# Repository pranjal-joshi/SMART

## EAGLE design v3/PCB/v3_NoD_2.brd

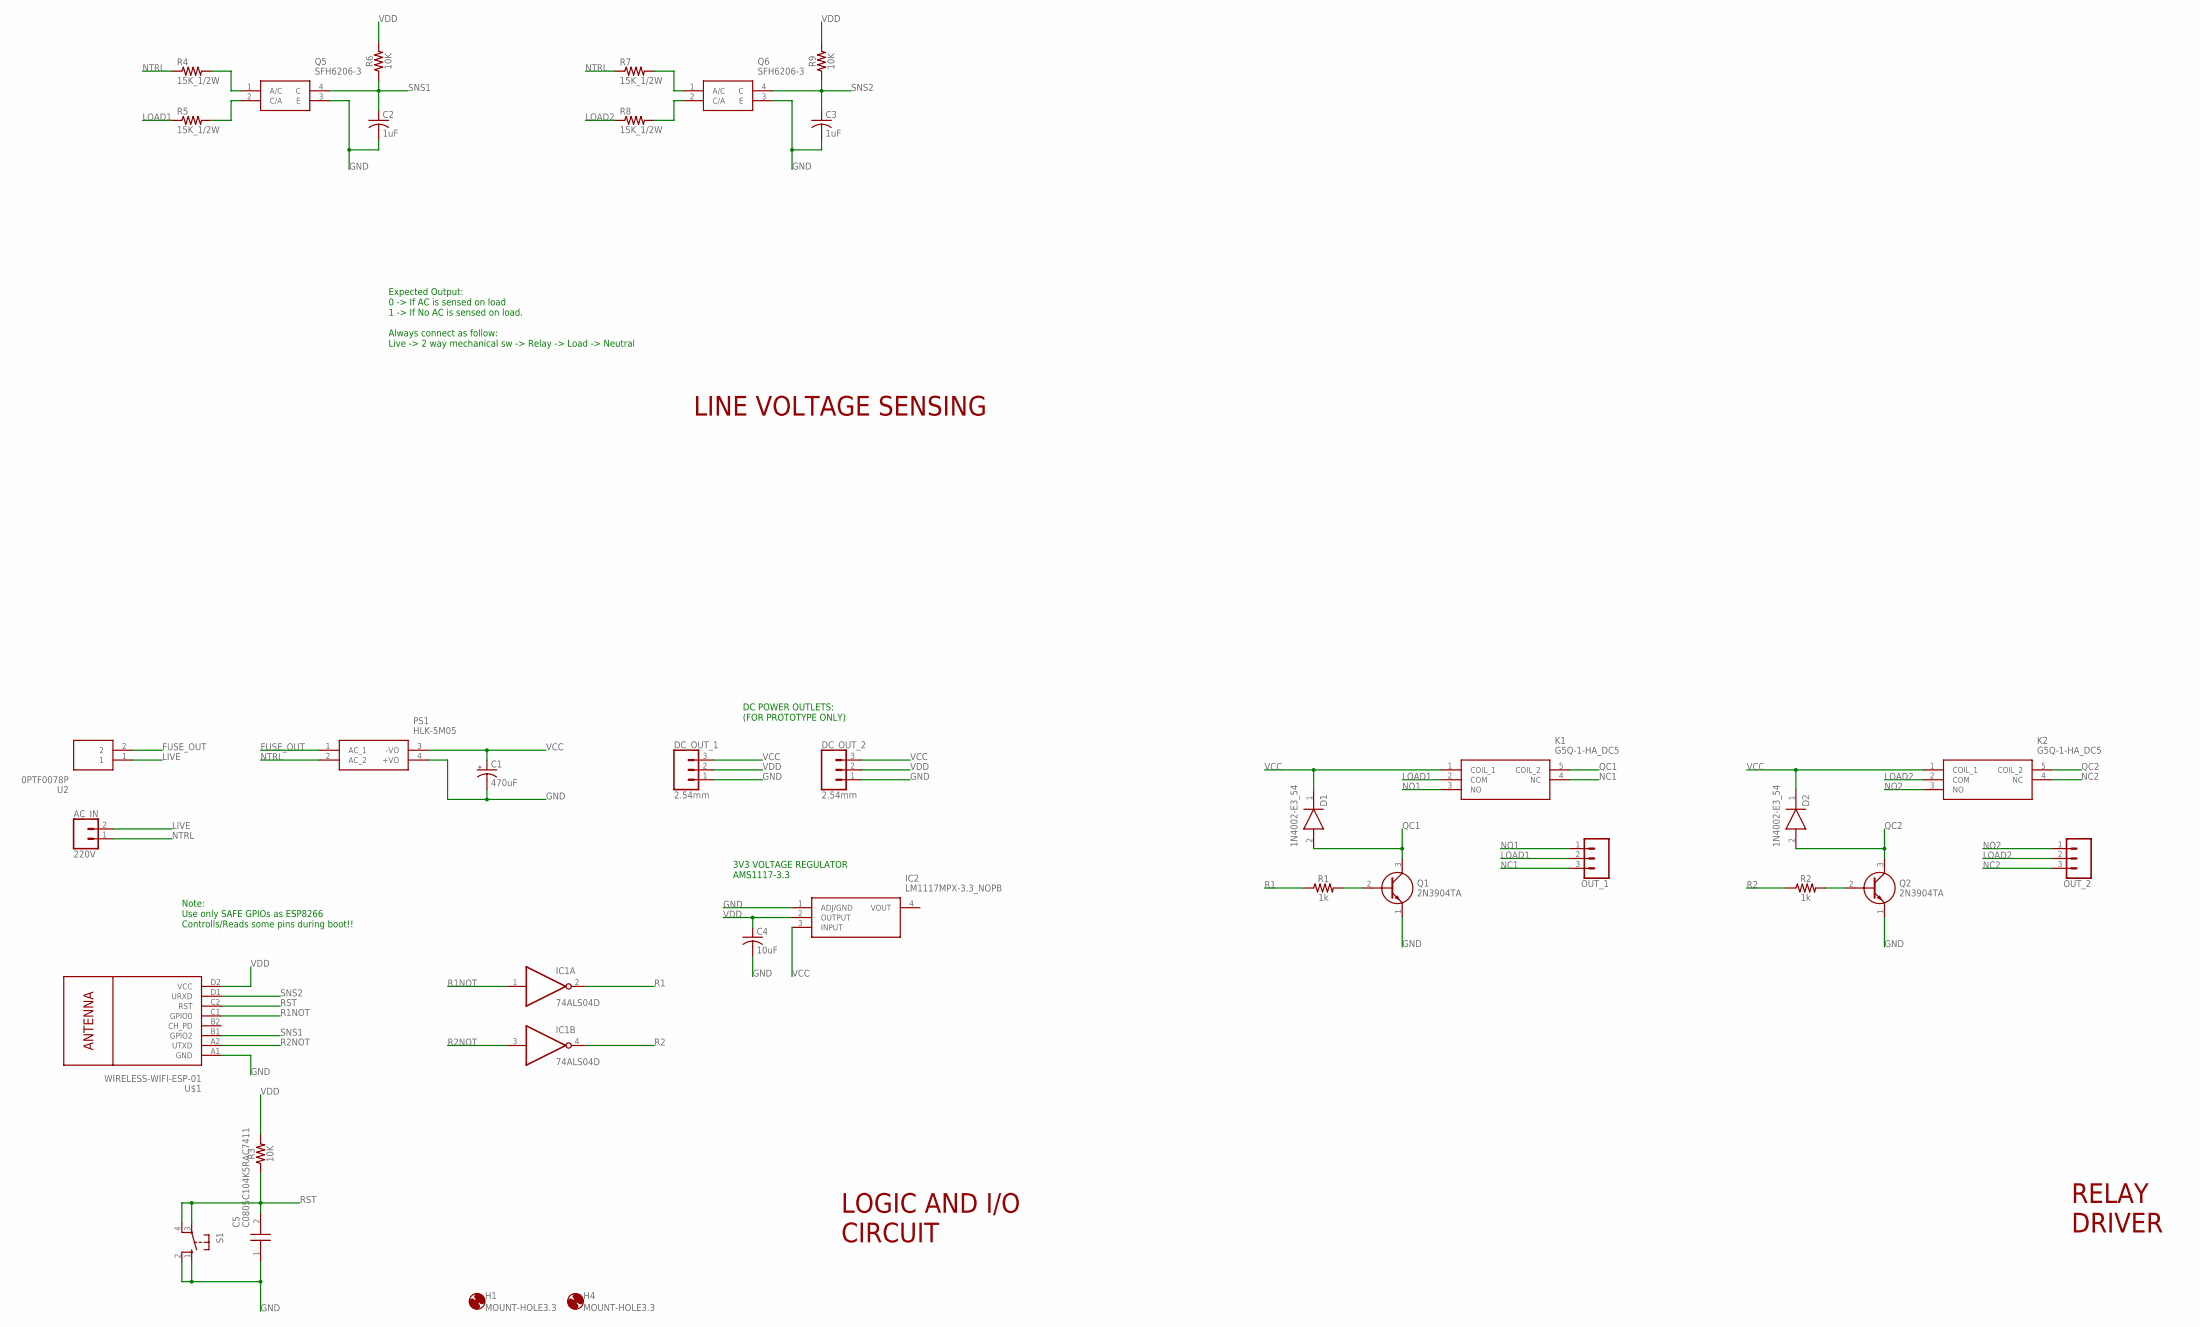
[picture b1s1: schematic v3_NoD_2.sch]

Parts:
AC_IN: 220V; SCREWTERMINAL-5MM-2
C1: 470uF; CPOL-RADIAL-5MM-10MM-KIT
C2, C3: 1uF; C0805
C4: 10uF; C0805
C5: C0805C104K5RAC7411; CAPC2012X88N
D1, D2: 1N4002-E3_54; DIOAD1405W86L465D235
DC_OUT_1, DC_OUT_2: 2.54mm; 1X03
H1, H4: MOUNT-HOLE3.3; 3,3
IC1: 74ALS04D; SO14
IC2: LM1117MPX-3.3_NOPB; SOT230P700X180-4N
K1, K2: G5Q-1-HA_DC5; G5Q1EU12DC
OUT_1, OUT_2: CONN_03-SCREW-5MM; SCREWTERMINAL-5MM-3
PS1: HLK-5M05; HLK5M05
Q1, Q2: 2N3904TA; BC33740TA
Q5, Q6: SFH6206-3; SOP254P1005X410-4N
R1, R2: 1k; 0603
R3, R6, R9: 10K; 0603
R4, R5, R7, R8: 15K_1/2W; R1210
S1: 10-XX; B3F-10XX
U2: 0PTF0078P
U$1: WIRELESS-WIFI-ESP-01

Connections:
FUSE_OUT: PS1.1 (AC_1), U2.2
GND: C1.-, C2.2, C3.2, C4.2, C5.1, DC_OUT_1.1, DC_OUT_2.1, IC1.7 (GND), IC2.1 (ADJ/GND), PS1.4 (+VO), Q1.1 (E), Q2.1 (E), Q5.3 (E), Q6.3 (E), S1.1 (S), S1.2 (S1), U$1.A1 (GND)
LIVE: AC_IN.2, U2.1
LOAD1: K1.2 (COM), OUT_1.2, R5.1
LOAD2: K2.2 (COM), OUT_2.2, R8.1
unnamed: Q5.1 (A/C), R4.2
unnamed: Q5.2 (C/A), R5.2
unnamed: Q6.1 (A/C), R7.2
unnamed: Q1.2 (B), R1.2
unnamed: Q2.2 (B), R2.2
unnamed: Q6.2 (C/A), R8.2
NC1: K1.4 (NC), OUT_1.3
NC2: K2.4 (NC), OUT_2.3
NO1: K1.3 (NO), OUT_1.1
NO2: K2.3 (NO), OUT_2.1
NTRL: AC_IN.1, PS1.2 (AC_2), R4.1, R7.1
QC1: D1.2 (A), K1.5 (COIL_2), Q1.3 (C)
QC2: D2.2 (A), K2.5 (COIL_2), Q2.3 (C)
R1: IC1.2 (O), R1.1
R1NOT: IC1.1 (I), U$1.C1 (GPIO0)
R2: IC1.4 (O), R2.1
R2NOT: IC1.3 (I), U$1.A2 (UTXD)
RST: C5.2, R3.1, S1.3, S1.4 (P1), U$1.C2 (RST)
SNS1: C2.1, Q5.4 (C), R6.1, U$1.B1 (GPIO2)
SNS2: C3.1, Q6.4 (C), R9.1, U$1.D1 (URXD)
VCC: C1.+, D1.1 (K), D2.1 (K), DC_OUT_1.3, DC_OUT_2.3, IC1.14 (VCC), IC2.3 (INPUT), K1.1 (COIL_1), K2.1 (COIL_1), PS1.3 (-VO)
VDD: C4.1, DC_OUT_1.2, DC_OUT_2.2, IC2.2 (OUTPUT), R3.2, R6.2, R9.2, U$1.D2 (VCC)

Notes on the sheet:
LOGIC AND I/O CIRCUIT
LINE VOLTAGE SENSING
RELAY DRIVER
DC POWER OUTLETS: (FOR PROTOTYPE ONLY)
Expected Output: 0 -> If AC is sensed on load 1 -> If No AC is sensed on load. Always connect as follow: Live -> 2 way mechanical sw -> Relay -> Load -> Neutral
Note: Use only SAFE GPIOs as ESP8266 Controlls/Reads some pins during boot!!
3V3 VOLTAGE REGULATOR AMS1117-3.3

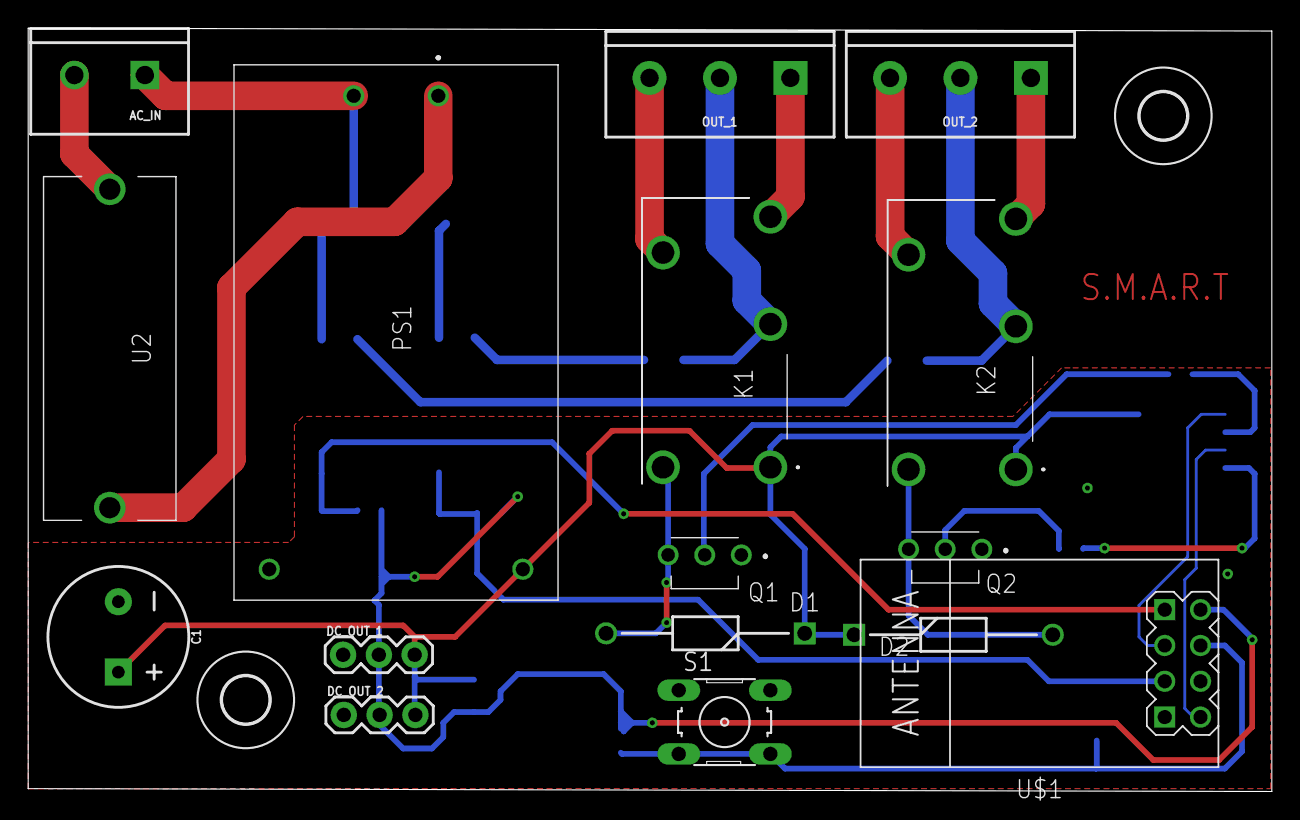
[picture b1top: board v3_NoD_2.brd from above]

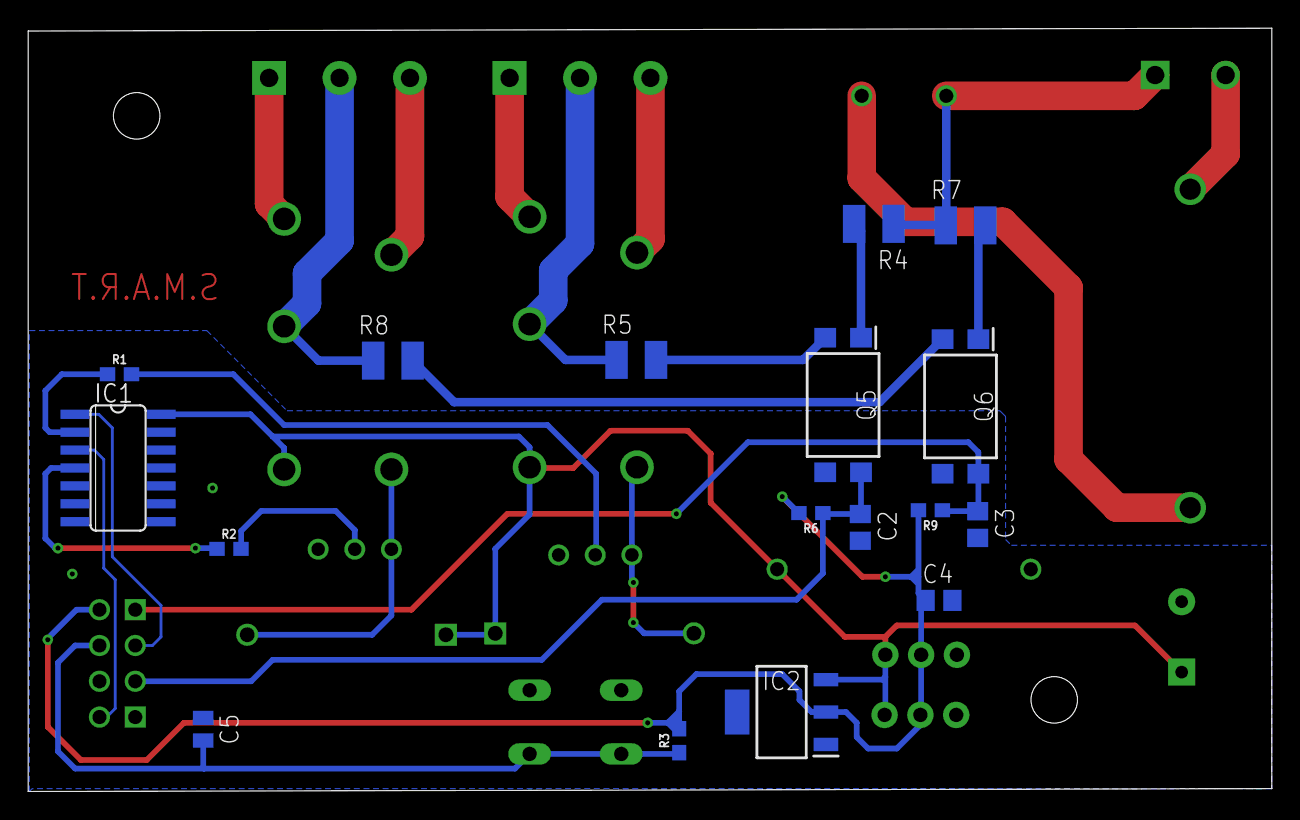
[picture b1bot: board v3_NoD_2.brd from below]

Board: 2 copper layers, 88.3 x 54.2 mm, 35 parts (17 on the bottom side), 27 nets.

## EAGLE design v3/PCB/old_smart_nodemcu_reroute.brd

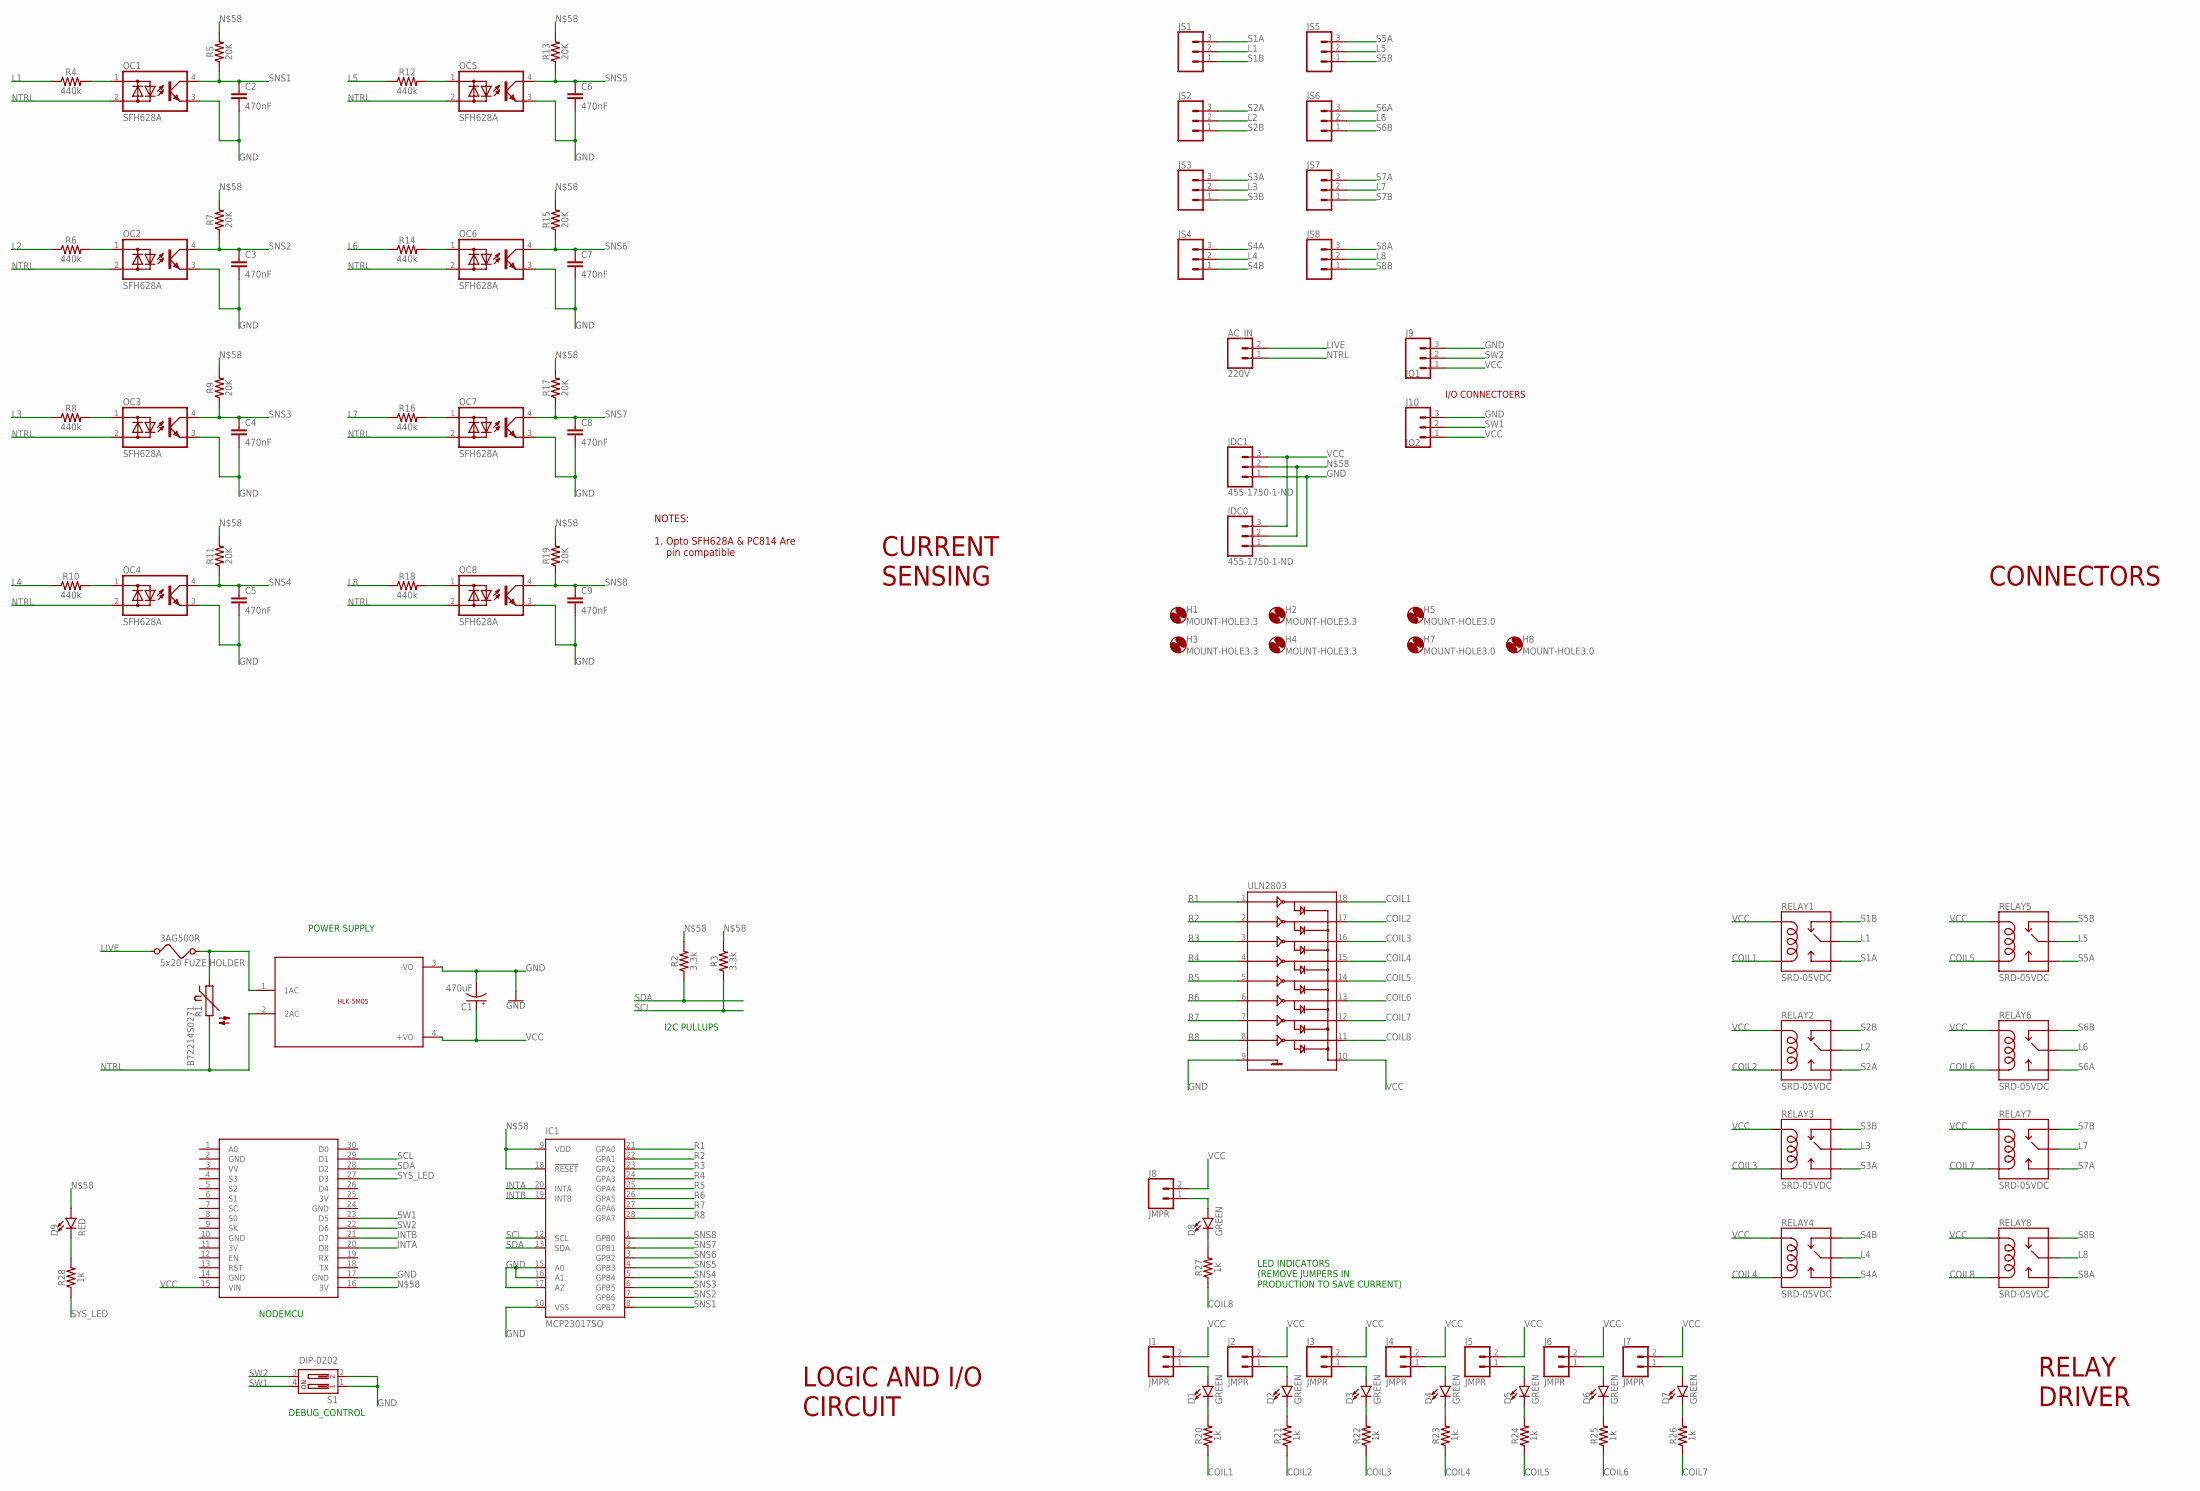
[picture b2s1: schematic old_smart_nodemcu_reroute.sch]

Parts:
3AG500R: 5x20 FUZE HOLDER; FUSE
AC_IN: 220V; SCREWTERMINAL-5MM-2
C1: 470uF; E3,5-8
C2, C3, C4, C5, C6, C7, C8, C9: 470nF; 0603
D1, D2, D3, D4, D5, D6, D7, D8: GREEN; LED-0603
D9: RED; LED-0603
H1, H2, H3, H4: MOUNT-HOLE3.3; 3,3
H5, H7, H8: MOUNT-HOLE3.0; 3,0
IC1: MCP23017SO; SO28W
J1, J2, J3, J4, J5, J6, J7, J8: JMPR; 1X02
J9: IO1; 1X03
J10: IO2; 1X03
JDC0, JDC1: 455-1750-1-ND; 1X03
JS1, JS2, JS3, JS4, JS5, JS6, JS7, JS8: CONN_03-SCREW-5MM; SCREWTERMINAL-5MM-3
NODEMCU: NODEMCU
OC1, OC2, OC3, OC4, OC5, OC6, OC7, OC8: SFH628A; DIL4-SMD
R1: B72214S0271; P592
R2, R3: 3.3k; 0603
R4, R6, R8, R10, R12, R14, R16, R18: 440k; 0805
R5, R7, R9, R11, R13, R15, R17, R19: 20K; 0603
R20, R21, R22, R23, R24, R25, R26, R27, R28: 1k; 0603
RELAY1, RELAY2, RELAY3, RELAY4, RELAY5, RELAY6, RELAY7, RELAY8: SRD-05VDC; SRD-05VDC-SL-C
S1: DIP-0202; DIPSWITCH-02
U$1: 5VDC/5W; HLK-5M05
ULN2803: ULN2803SOICW; SO18L

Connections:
3V: NODEMCU.11 (3V), NODEMCU.25 (3V)
COIL1: R20.1, RELAY1.COIL0, ULN2803.18
COIL2: R21.1, RELAY2.COIL0, ULN2803.17
COIL3: R22.1, RELAY3.COIL0, ULN2803.16
COIL4: R23.1, RELAY4.COIL0, ULN2803.15
COIL5: R24.1, RELAY5.COIL0, ULN2803.14
COIL6: R25.1, RELAY6.COIL0, ULN2803.13
COIL7: R26.1, RELAY7.COIL0, ULN2803.12
COIL8: R27.1, RELAY8.COIL0, ULN2803.11
GND: C1.-, C2.2, C3.2, C4.2, C5.2, C6.2, C7.2, C8.2, C9.2, IC1.10 (VSS), IC1.15 (A0), IC1.16 (A1), IC1.17 (A2), J9.3, J10.3, JDC0.1, JDC1.1, NODEMCU.2 (GND), NODEMCU.10 (GND), NODEMCU.14 (GND), NODEMCU.17 (GND), NODEMCU.24 (GND), OC1.3 (E), OC2.3 (E), OC3.3 (E), OC4.3 (E), OC5.3 (E), OC6.3 (E), OC7.3 (E), OC8.3 (E), S1.1, S1.2, U$1.3 (-VO), ULN2803.9
INTA: IC1.20 (INTA), NODEMCU.20 (D8)
INTB: IC1.19 (INTB), NODEMCU.21 (D7)
L1: JS1.2, R4.1, RELAY1.SWCOMMON
L2: JS2.2, R6.1, RELAY2.SWCOMMON
L3: JS3.2, R8.1, RELAY3.SWCOMMON
L4: JS4.2, R10.1, RELAY4.SWCOMMON
L5: JS5.2, R12.1, RELAY5.SWCOMMON
L6: JS6.2, R14.1, RELAY6.SWCOMMON
L7: JS7.2, R16.1, RELAY7.SWCOMMON
L8: JS8.2, R18.1, RELAY8.SWCOMMON
LIVE: 3AG500R.1, AC_IN.2
LIVE_FUSE: 3AG500R.2, R1.1, U$1.1 (1AC)
unnamed: OC1.1 (AC1), R4.2
unnamed: OC2.1 (AC1), R6.2
unnamed: OC3.1 (AC1), R8.2
unnamed: D1.A, J1.1
unnamed: OC5.1 (AC1), R12.2
unnamed: OC6.1 (AC1), R14.2
unnamed: OC7.1 (AC1), R16.2
unnamed: OC4.1 (AC1), R10.2
unnamed: OC8.1 (AC1), R18.2
unnamed: D1.C, R20.2
unnamed: D2.A, J2.1
unnamed: D2.C, R21.2
unnamed: D3.A, J3.1
unnamed: D3.C, R22.2
unnamed: D4.A, J4.1
unnamed: D4.C, R23.2
unnamed: D5.A, J5.1
unnamed: D5.C, R24.2
unnamed: D6.A, J6.1
unnamed: D6.C, R25.2
unnamed: D7.A, J7.1
unnamed: D7.C, R26.2
unnamed: D8.A, J8.1
unnamed: D8.C, R27.2
unnamed: D9.C, R28.2
unnamed: D9.A, IC1.9 (VDD), IC1.18 (!RESET), JDC0.2, JDC1.2, NODEMCU.16 (3V), R2.2, R3.2, R5.2, R7.2, R9.2, R11.2, R13.2, R15.2, R17.2, R19.2
NTRL: AC_IN.1, OC1.2 (AC2), OC2.2 (AC2), OC3.2 (AC2), OC4.2 (AC2), OC5.2 (AC2), OC6.2 (AC2), OC7.2 (AC2), OC8.2 (AC2), R1.2, U$1.2 (2AC)
R1: IC1.21 (GPA0), ULN2803.1
R2: IC1.22 (GPA1), ULN2803.2
R3: IC1.23 (GPA2), ULN2803.3
R4: IC1.24 (GPA3), ULN2803.4
R5: IC1.25 (GPA4), ULN2803.5
R6: IC1.26 (GPA5), ULN2803.6
R7: IC1.27 (GPA6), ULN2803.7
R8: IC1.28 (GPA7), ULN2803.8
S1A: JS1.3, RELAY1.SWOPEN
S1B: JS1.1, RELAY1.SWCLOSED (SWCLOSE)
S2A: JS2.3, RELAY2.SWOPEN
S2B: JS2.1, RELAY2.SWCLOSED (SWCLOSE)
S3A: JS3.3, RELAY3.SWOPEN
S3B: JS3.1, RELAY3.SWCLOSED (SWCLOSE)
S4A: JS4.3, RELAY4.SWOPEN
S4B: JS4.1, RELAY4.SWCLOSED (SWCLOSE)
S5A: JS5.3, RELAY5.SWOPEN
S5B: JS5.1, RELAY5.SWCLOSED (SWCLOSE)
S6A: JS6.3, RELAY6.SWOPEN
S6B: JS6.1, RELAY6.SWCLOSED (SWCLOSE)
S7A: JS7.3, RELAY7.SWOPEN
S7B: JS7.1, RELAY7.SWCLOSED (SWCLOSE)
S8A: JS8.3, RELAY8.SWOPEN
S8B: JS8.1, RELAY8.SWCLOSED (SWCLOSE)
SCL: IC1.12 (SCL), NODEMCU.29 (D1), R3.1
SDA: IC1.13 (SDA), NODEMCU.28 (D2), R2.1
SNS1: C2.1, IC1.8 (GPB7), OC1.4 (C), R5.1
SNS2: C3.1, IC1.7 (GPB6), OC2.4 (C), R7.1
SNS3: C4.1, IC1.6 (GPB5), OC3.4 (C), R9.1
SNS4: C5.1, IC1.5 (GPB4), OC4.4 (C), R11.1
SNS5: C6.1, IC1.4 (GPB3), OC5.4 (C), R13.1
SNS6: C7.1, IC1.3 (GPB2), OC6.4 (C), R15.1
SNS7: C8.1, IC1.2 (GPB1), OC7.4 (C), R17.1
SNS8: C9.1, IC1.1 (GPB0), OC8.4 (C), R19.1
SW1: J10.2, NODEMCU.23 (D5), S1.4
SW2: J9.2, NODEMCU.22 (D6), S1.3
SYS_LED: NODEMCU.27 (D3), R28.1
VCC: C1.+, J1.2, J2.2, J3.2, J4.2, J5.2, J6.2, J7.2, J8.2, J9.1, J10.1, JDC0.3, JDC1.3, NODEMCU.15 (VIN), RELAY1.COIL1, RELAY2.COIL1, RELAY3.COIL1, RELAY4.COIL1, RELAY5.COIL1, RELAY6.COIL1, RELAY7.COIL1, RELAY8.COIL1, U$1.4 (+VO), ULN2803.10

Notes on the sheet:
NODEMCU
POWER SUPPLY
I2C PULLUPS
LOGIC AND I/O CIRCUIT
CURRENT SENSING
RELAY DRIVER
LED INDICATORS (REMOVE JUMPERS IN PRODUCTION TO SAVE CURRENT)
DEBUG_CONTROL
CONNECTORS
NOTES: 1. Opto SFH628A & PC814 Are pin compatible
I/O CONNECTOERS

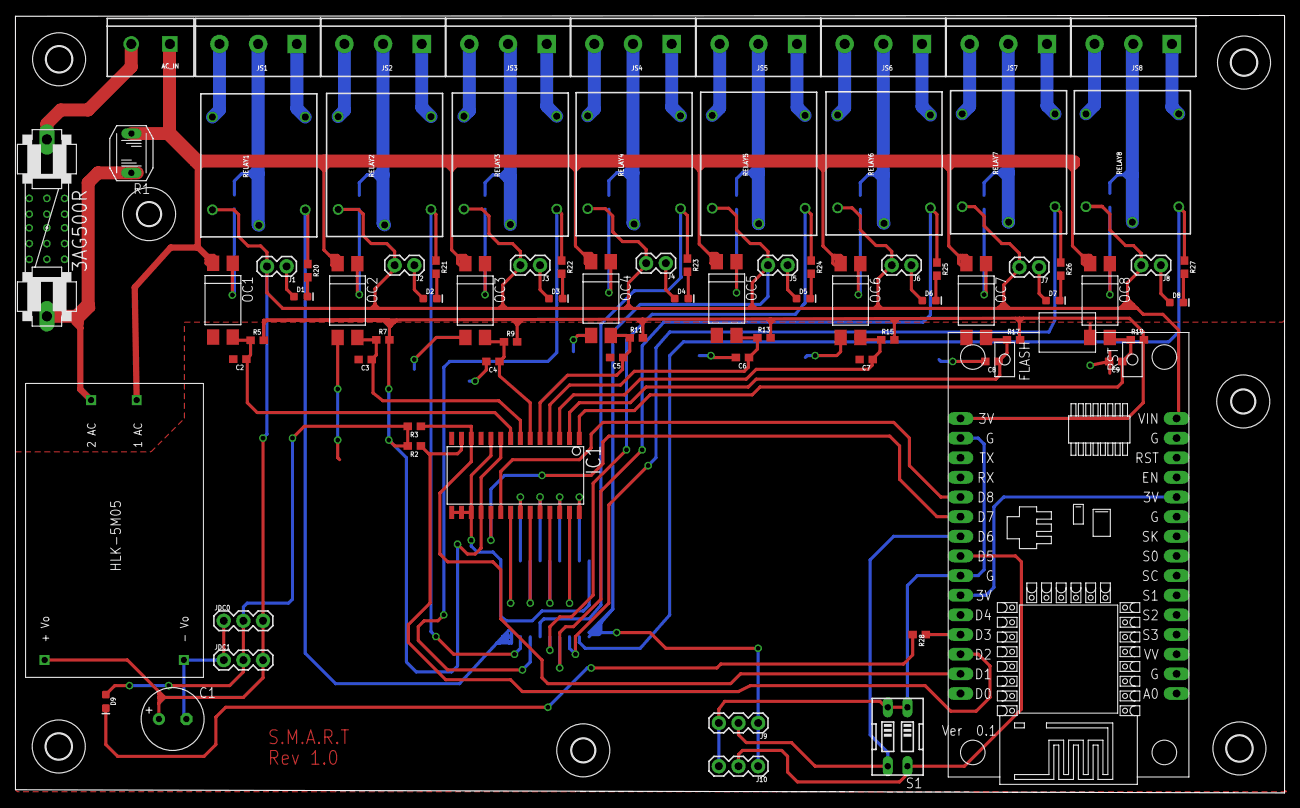
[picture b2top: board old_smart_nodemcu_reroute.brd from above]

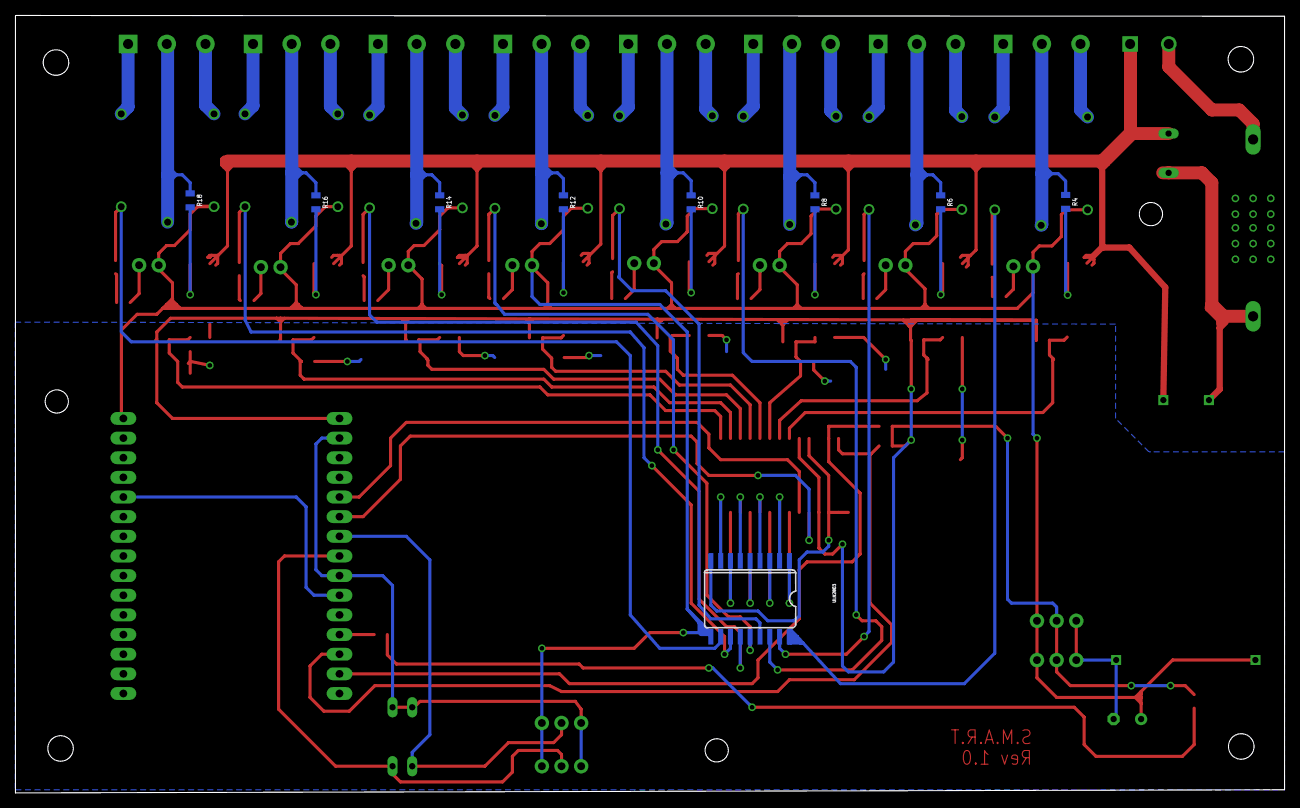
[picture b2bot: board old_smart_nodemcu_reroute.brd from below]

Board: 2 copper layers, 164.1 x 100.5 mm, 96 parts (9 on the bottom side), 87 nets.

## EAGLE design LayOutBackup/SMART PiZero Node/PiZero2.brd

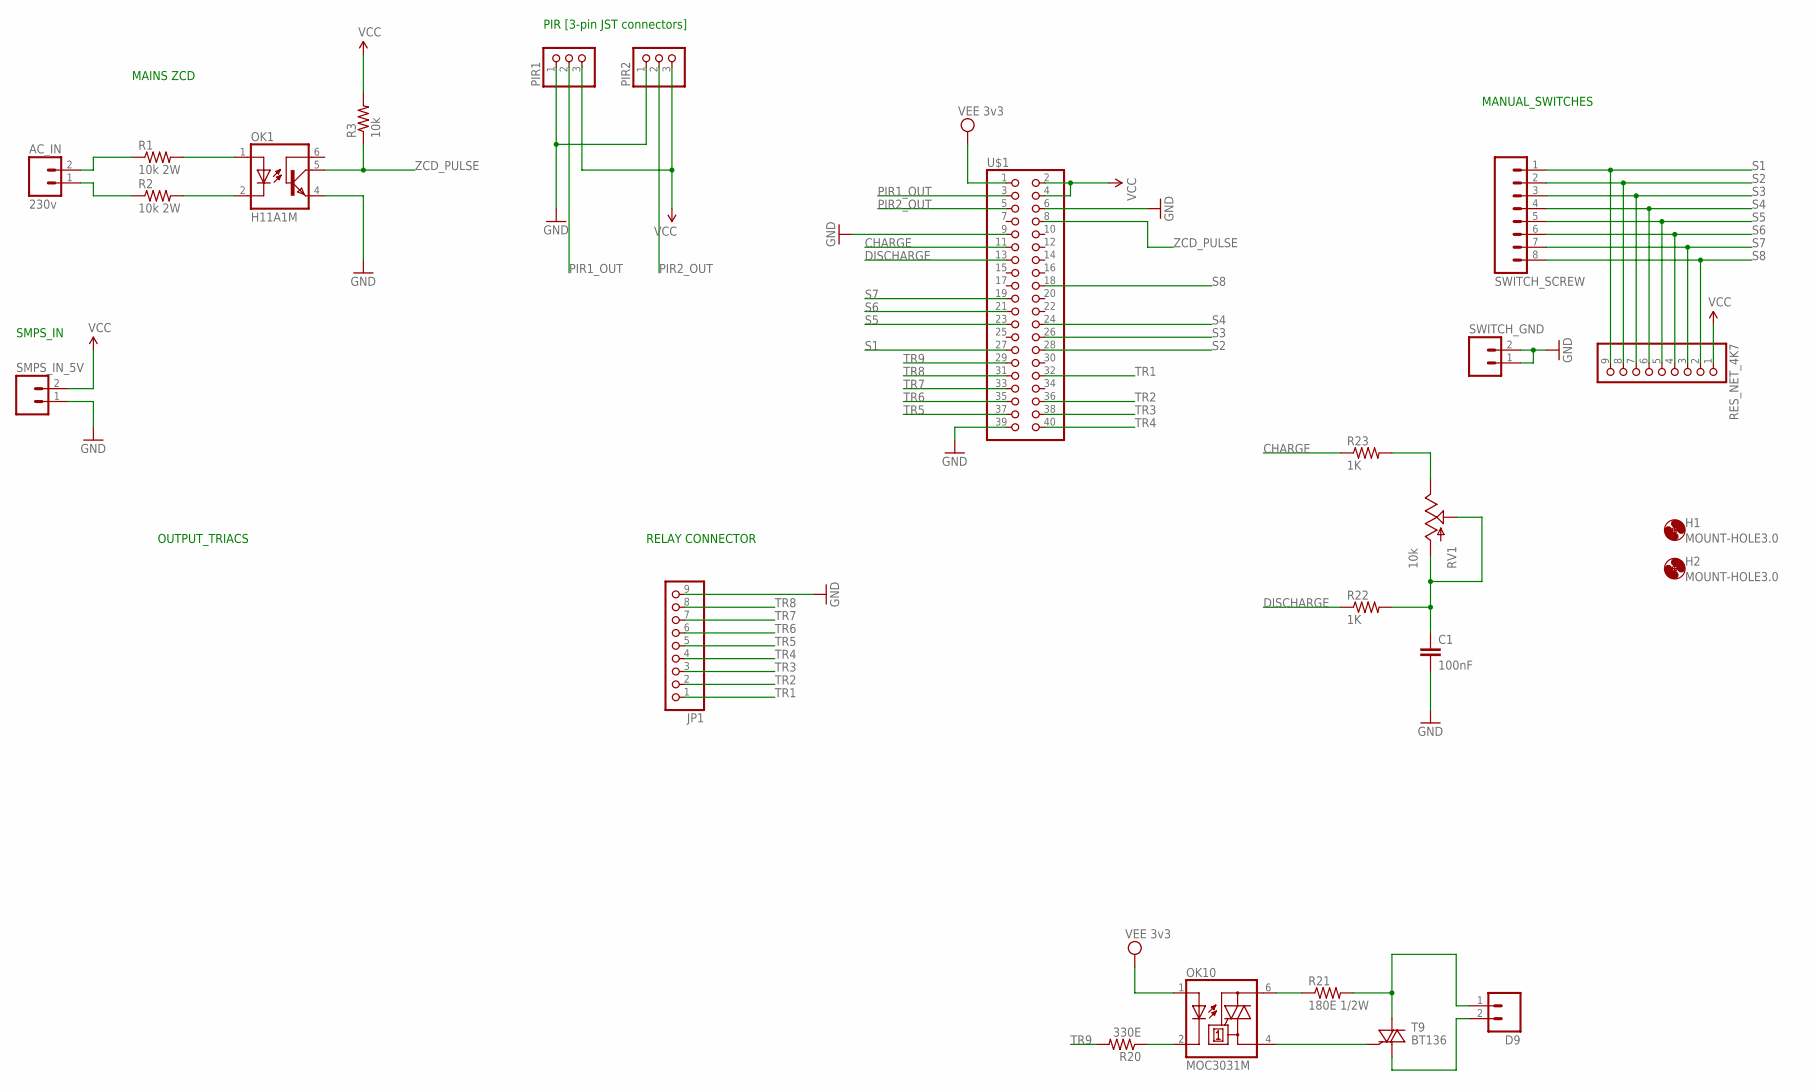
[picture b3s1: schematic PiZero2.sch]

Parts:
AC_IN: 230v; SCREWTERMINAL-3.5MM-2_LOCK
C1: 100nF; C025-025X050
D9: M023.5MM_LOCK; SCREWTERMINAL-3.5MM-2_LOCK
H1, H2: MOUNT-HOLE3.0; 3,0
JP1: PINHD-1X9/90; 1X09/90
OK1: H11A1M; DIL06
OK10: MOC3031M; DIL06
PIR1, PIR2: PINHD-1X3; 1X03
R1, R2: 10k 2W; AXIAL-0.8
R3: 10k; AXIAL-0.4
R20: 330E; AXIAL-0.4
R21: 180E 1/2W; AXIAL-0.5
R22, R23: 1K; AXIAL-0.4
RES_NET_4K7: PINHD-1X9; 1X09
RV1: 10k; 3362U
SMPS_IN_5V: M023.5MM_LOCK; SCREWTERMINAL-3.5MM-2_LOCK
SWITCH_GND: M023.5MM; SCREWTERMINAL-3.5MM-2
SWITCH_SCREW: M083.5MM-8; SCREWTERMINAL-3.5MM-8
T9: BT136; TO220AB
U$1: PINHD-2X20; 2X20

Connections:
CHARGE: R23.P$1 (1), U$1.11
DISCHARGE: R22.P$1 (1), U$1.13
GND: C1.2, JP1.9, OK1.4 (EMI), PIR1.1, PIR2.1, SMPS_IN_5V.1, SWITCH_GND.1, SWITCH_GND.2, U$1.6, U$1.9, U$1.39
unnamed: AC_IN.2, R1.P$1 (1)
unnamed: AC_IN.1, R2.P$1 (1)
unnamed: OK1.1 (A), R1.P$2 (2)
unnamed: OK1.2 (C), R2.P$2 (2)
unnamed: OK10.6 (A2), R21.P$1 (1)
unnamed: D9.1, R21.P$2 (2), T9.2 (A2)
unnamed: OK10.4 (A1), T9.3 (G)
unnamed: D9.2, T9.1 (A1)
unnamed: OK10.2 (C), R20.P$1 (1)
unnamed: C1.1, R22.P$2 (2), RV1.P$2 (S), RV1.P$3 (A)
unnamed: R23.P$2 (2), RV1.P$1 (E)
PIR1_OUT: PIR1.2, U$1.3
PIR2_OUT: PIR2.2, U$1.5
S1: RES_NET_4K7.9, SWITCH_SCREW.1, U$1.27
S2: RES_NET_4K7.8, SWITCH_SCREW.2, U$1.28
S3: RES_NET_4K7.7, SWITCH_SCREW.3, U$1.26
S4: RES_NET_4K7.6, SWITCH_SCREW.4, U$1.24
S5: RES_NET_4K7.5, SWITCH_SCREW.5, U$1.23
S6: RES_NET_4K7.4, SWITCH_SCREW.6, U$1.21
S7: RES_NET_4K7.3, SWITCH_SCREW.7, U$1.19
S8: RES_NET_4K7.2, SWITCH_SCREW.8, U$1.18
TR1: JP1.1, U$1.32
TR2: JP1.2, U$1.36
TR3: JP1.3, U$1.38
TR4: JP1.4, U$1.40
TR5: JP1.5, U$1.37
TR6: JP1.6, U$1.35
TR7: JP1.7, U$1.33
TR8: JP1.8, U$1.31
TR9: R20.P$2 (2), U$1.29
VCC: PIR1.3, PIR2.3, R3.P$2 (2), RES_NET_4K7.1, SMPS_IN_5V.2, U$1.2, U$1.4
VEE: OK10.1 (A), U$1.1
ZCD_PULSE: OK1.5 (COL), R3.P$1 (1), U$1.8

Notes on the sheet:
MAINS ZCD
SMPS_IN
PIR [3-pin JST connectors]
OUTPUT_TRIACS
MANUAL_SWITCHES
RELAY CONNECTOR

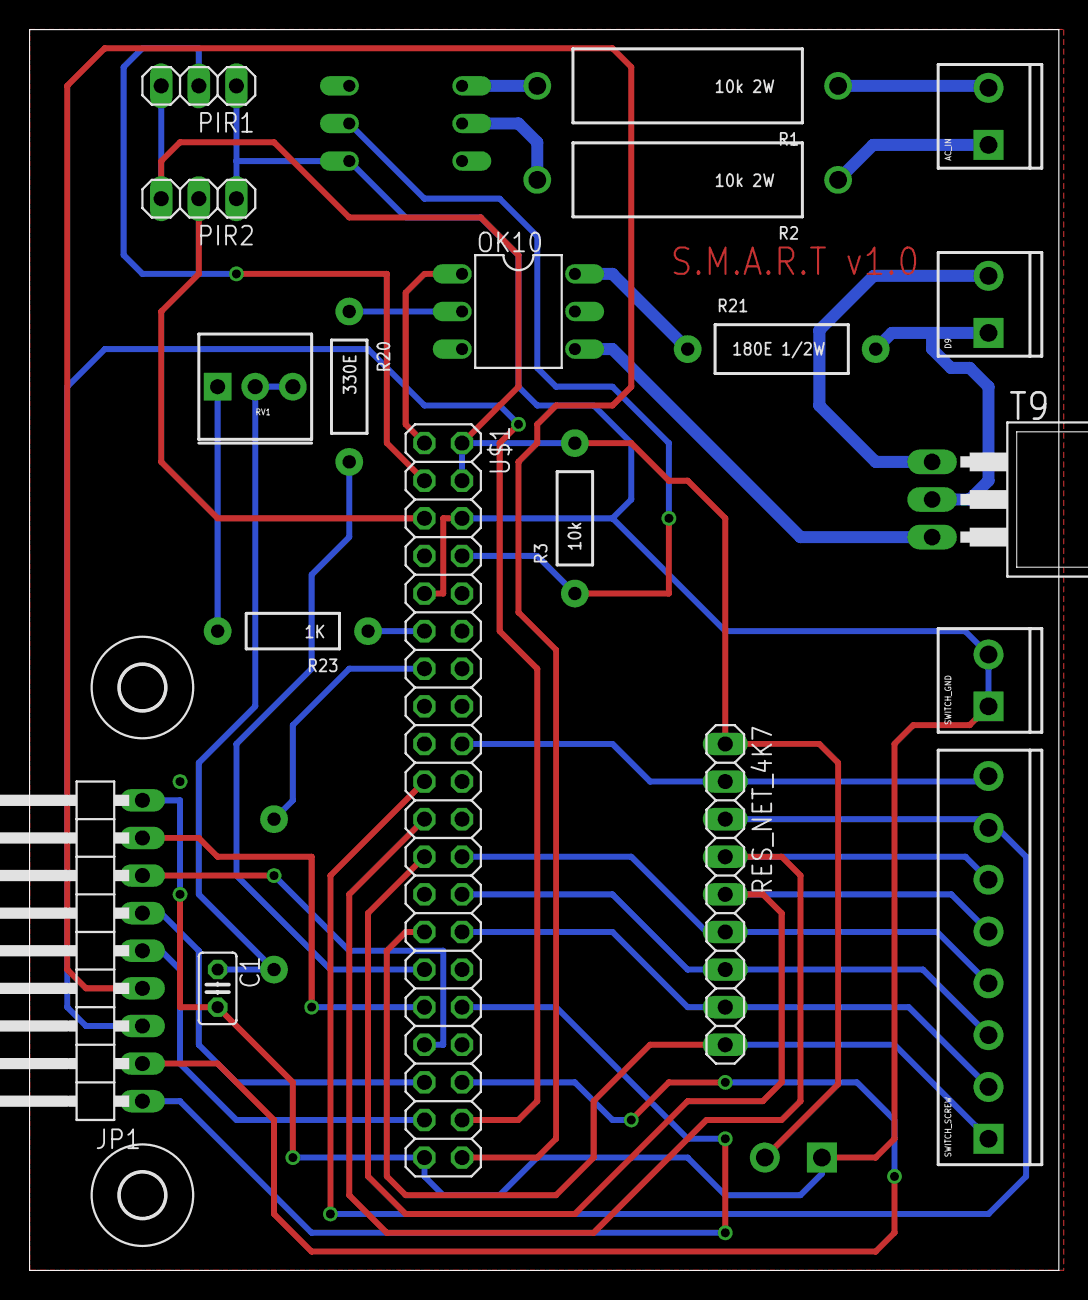
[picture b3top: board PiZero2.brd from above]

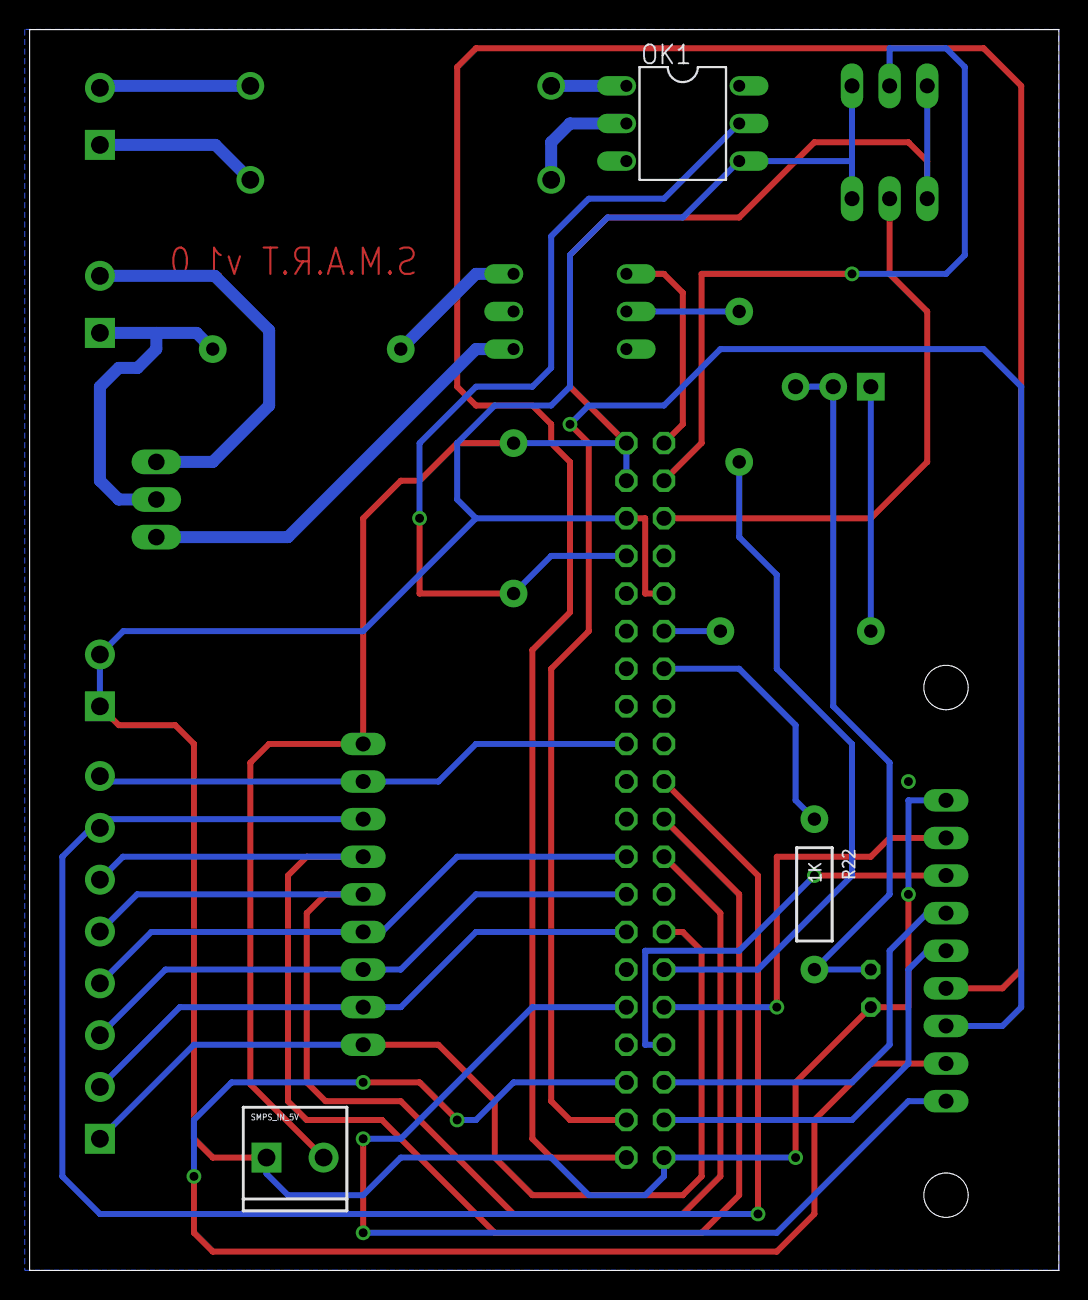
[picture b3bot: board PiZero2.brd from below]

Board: 2 copper layers, 69.5 x 83.8 mm, 24 parts (3 on the bottom side), 36 nets.

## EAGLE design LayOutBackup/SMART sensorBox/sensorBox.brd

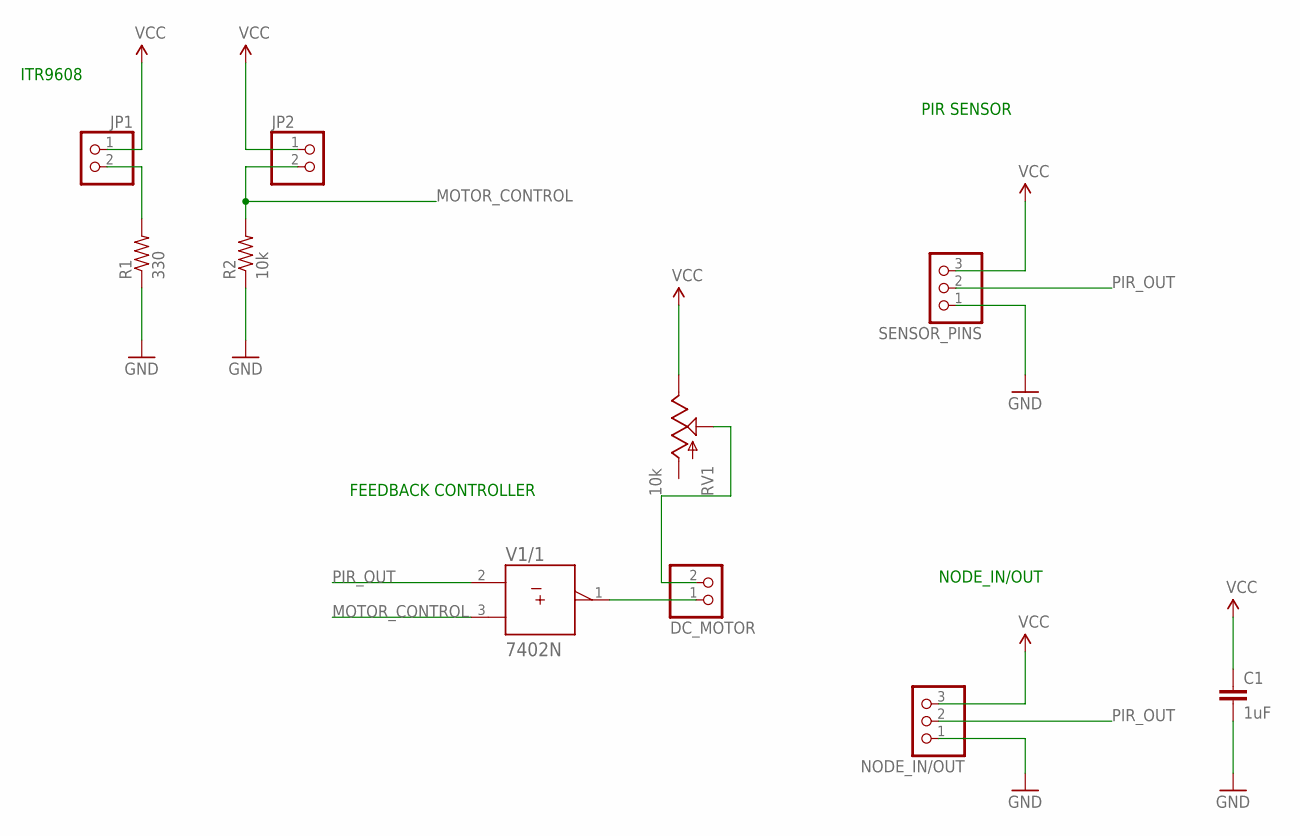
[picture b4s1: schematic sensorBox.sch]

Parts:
C1: 1uF; CAP-PTH-SMALL
DC_MOTOR: PINHD-1X2; 1X02
JP1, JP2: PINHD-1X2; 1X02
NODE_IN/OUT: PINHD-1X3; 1X03
R1: 330; AXIAL-0.4
R2: 10k; AXIAL-0.4
RV1: 10k; TRIM_POT
SENSOR_PINS: PINHD-1X3; 1X03
V1: 7402N; DIL14

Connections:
+UB: V1.14 (+UB)
-UB: V1.7 (-UB)
GND: C1.2, NODE_IN/OUT.1, R1.P$1 (1), R2.P$1 (1), SENSOR_PINS.1
MOTOR_CONTROL: JP2.2, R2.P$2 (2), V1.3 (B)
unnamed: JP1.2, R1.P$2 (2)
unnamed: DC_MOTOR.2, RV1.1 (S)
unnamed: DC_MOTOR.1, V1.1 (Y)
PIR_OUT: NODE_IN/OUT.2, SENSOR_PINS.2, V1.2 (A)
VCC: C1.1, JP1.1, JP2.1, NODE_IN/OUT.3, RV1.2 (E), SENSOR_PINS.3

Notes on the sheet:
ITR9608
FEEDBACK CONTROLLER
PIR SENSOR
NODE_IN/OUT

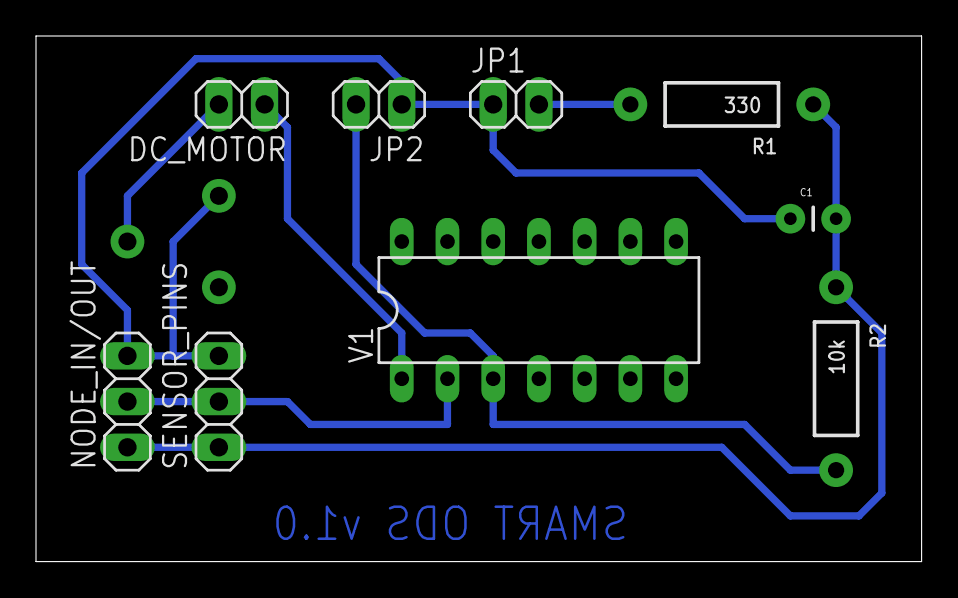
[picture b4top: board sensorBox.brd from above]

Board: 2 copper layers, 49.2 x 29.2 mm, 10 parts (1 on the bottom side), 7 nets.

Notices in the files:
parts and their libraries:
SparkFun-Connectors: Licensing: Creative Commons ShareAlike 4.0 International - https://creativecommons.org/licenses/by-sa/4.0
ESP-01: Released under the Creative Commons Attribution 4.0 International License: http://creativecommons.org/licenses/by/4.0
